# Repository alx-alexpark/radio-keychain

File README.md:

# radio-keychain
A fully-functional FM receiver in a 3x3cm footprint, perfect for a keychain.

It uses the connected headphones as an antenna, and is powered off a CR2032 coin cell. The FM tuner used is the Si4702, which supports the 76-108MHz frequency range.

Based on the CH32v003, this radio runs on RISC-V!

## Motivation
I love radio, and I wanted to make the tiniest keychain radio possible. I also thought it would be interesting to learn how radios work.

## How to use
First, connect a pair of headphones or an aux cable, this is your antenna. There are 4 buttons on the device, a volume up/down, and a frequency up/down. First, set the volume to a confortable level, and then use the frequency up/down buttons to step up and down 0.1MHz until you find a station. Then, enjoy listening to the station!

## Schematic and PCB
https://kicanvas.org/?repo=https://github.com/alx-alexpark/radio-keychain

## Zine

## Bill of Materials

| Designator | Footprint | Quantity | Value | LCSC Part # |
|---|---|---|---|---|
| BT1 | BAT-SMD_MY-2032-12 | 1 | MY-2032-12 | [C964833](https://www.lcsc.com/product-detail/C964833.html) |
| C1, C6 | 0402 | 2 | 100nF | [C1525](https://www.lcsc.com/product-detail/C1525.html) |
| C2 | 0402 | 1 | 100pF | [C1546](https://www.lcsc.com/product-detail/C1546.html) |
| C3, C4 | 0603 | 2 | 0.47uF | [C1623](https://www.lcsc.com/product-detail/C1623.html) |
| C5, C7, C8 | 0603 | 3 | 1uF | [C1592](https://www.lcsc.com/product-detail/C1592.html) |
| C9 | 0402 | 1 | 22nF | [C1532](https://www.lcsc.com/product-detail/C1532.html) |
| CN1 | PJ-320D | 1 | PJ-320D | [C431535](https://www.lcsc.com/product-detail/C431535.html) |
| D1 | 0402 | 1 | LED | [C2286](https://www.lcsc.com/product-detail/C2286.html) |
| FB1, FB2 | 0603 | 2 | BLM18BD252SN1D | [C77668](https://www.lcsc.com/product-detail/C77668.html) |
| J1 | PinHeader_1x03_P2.54mm_Vertical | 1 | Conn_01x03_Pin | — |
| L1 | 0603 | 1 | LQW18ANR27J00D | [C98093](https://www.lcsc.com/product-detail/C98093.html) |
| OSC1 | CRYSTAL-SMD_4P-L3.2-W2.5-BL | 1 | SX2M32_768KM20F30TNN | [C2901603](https://www.lcsc.com/product-detail/C2901603.html) |
| R1, R2, R3, R4, R5, R6 | 0603 | 6 | 10k | [C25804](https://www.lcsc.com/product-detail/C25804.html) |
| R10, R9 | 0402 | 2 | 2k | [C4109](https://www.lcsc.com/product-detail/C4109.html) |
| R11 | 0402 | 1 | 330 | [C25104](https://www.lcsc.com/product-detail/C25104.html) |
| R7, R8 | 0402 | 2 | 2.2k | [C25879](https://www.lcsc.com/product-detail/C25879.html) |
| SW1, SW2, SW3, SW4 | SW-SMD_4P-L4.2-W3.3-P2.15-LS5.1 | 4 | SW_Push_45deg | [C455282](https://www.lcsc.com/product-detail/C455282.html) |
| SW5 | SW-SMD_MST22D18G2 | 1 | K3-2235S-F1 | [C223858](https://www.lcsc.com/product-detail/C223858.html) |
| U1 | QFN-20-1EP_3x3mm_P0.4mm_EP1.65x1.65mm | 1 | CH32V003F4U6 | [C5299908](https://www.lcsc.com/product-detail/C5299908.html) |
| U2 | QFN-28_4x4mm_P0.5mm | 1 | TPA6130A2RTJR | [C130046](https://www.lcsc.com/product-detail/C130046.html) |
| U3 | MPS_QFN-16_3x3mm_P0.5mm | 1 | SI4702-C19-GMR | [C2155666](https://www.lcsc.com/product-detail/C2155666.html) |

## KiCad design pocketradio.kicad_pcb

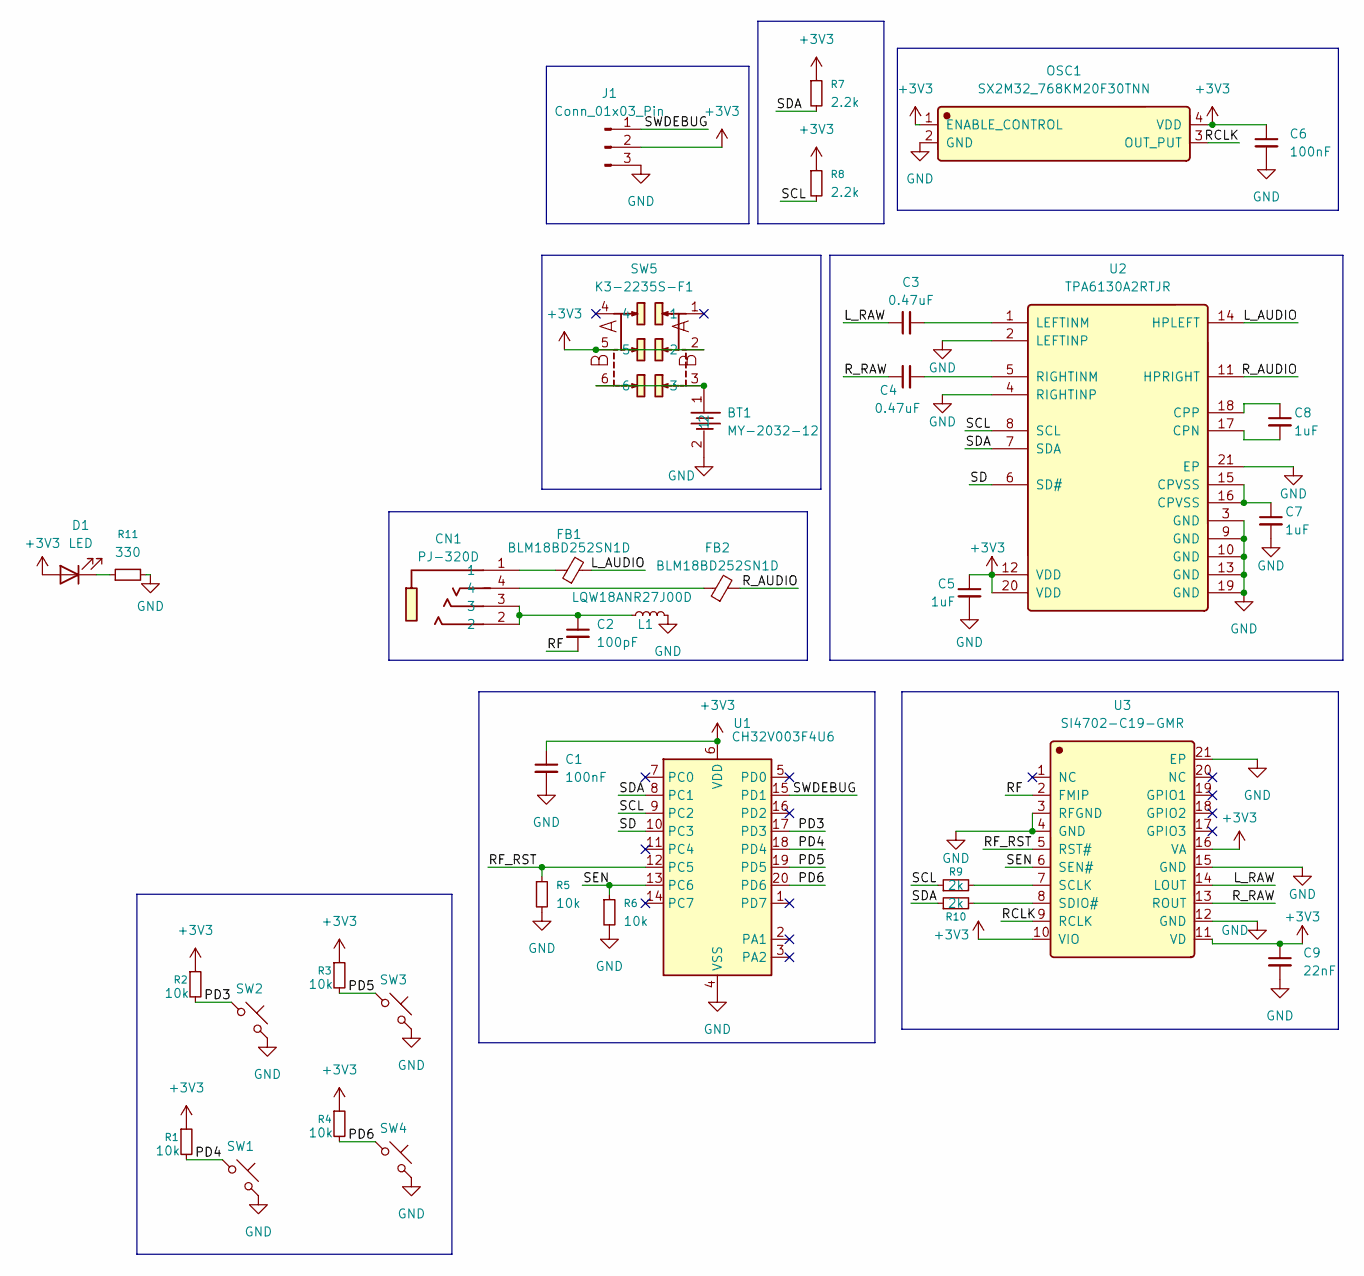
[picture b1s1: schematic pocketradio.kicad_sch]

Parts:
BT1: MY-2032-12; BAT-SMD_MY-2032-12; Manufacturer Part MY-2032-12; LCSC C964833
C1, C6: 100nF; C_0402_1005Metric; LCSC Part C1525
C2: 100pF; C_0402_1005Metric; LCSC Part C1546
C3, C4: 0.47uF; C_0603_1608Metric; LCSC Part C1623
C5, C7, C8: 1uF; C_0603_1608Metric; LCSC Part C1592
C9: 22nF; C_0402_1005Metric; LCSC Part C1532
CN1: PJ-320D; Manufacturer Part PJ-320D; LCSC C431535
D1: LED; LED_0402_1005Metric; LCSC Part C2286
FB1, FB2: BLM18BD252SN1D; L_0603_1608Metric; LCSC Part C77668
J1: Conn_01x03_Pin; PinHeader_1x03_P2.54mm_Vertical
L1: LQW18ANR27J00D; L_0603_1608Metric; LCSC Part C98093
OSC1: SX2M32_768KM20F30TNN; CRYSTAL-SMD_4P-L3.2-W2.5-BL; Manufacturer Part SX2M32.768KM20F30TNN; LCSC C2901603
R1, R2, R3, R4, R5, R6: 10k; R_0603_1608Metric; LCSC Part C25804
R7, R8: 2.2k; C_0402_1005Metric; LCSC Part C25879
R9, R10: 2k; R_0402_1005Metric; LCSC Part C4109
R11: 330; R_0402_1005Metric; LCSC Part C25104
SW1, SW2, SW3, SW4: SW_Push_45deg; SW-SMD_4P-L4.2-W3.3-P2.15-LS5.1; LCSC Part C455282
SW5: K3-2235S-F1; SW-SMD_MST22D18G2; Manufacturer Part K3-2235S-F1; LCSC C223858
U1: CH32V003F4U6; QFN-20-1EP_3x3mm_P0.4mm_EP1.65x1.65mm; LCSC C5299908
U2: TPA6130A2RTJR; QFN-28_4x4mm_P0.5mm; Manufacturer Part TPA6130A2RTJR; LCSC C130046
U3: SI4702-C19-GMR; MPS_QFN-16_3x3mm_P0.5mm; Manufacturer Part SI4702-C19-GMR; LCSC C2155666

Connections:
+3V3: C1.1, C5.1, C6.1, C9.1, D1.2 (A), J1.2, OSC1.1 (ENABLE_CONTROL), OSC1.4 (VDD), R1.1, R2.1, R3.1, R4.1, R7.1, R8.1, SW5.2, SW5.5, U1.6 (VDD), U2.12 (VDD), U2.20 (VDD), U3.10 (VIO), U3.11 (VD), U3.16 (VA)
/L_AUDIO: FB1.2, U2.14 (HPLEFT)
/L_RAW: C3.1, U3.14 (LOUT)
/PD3: R2.2, SW2.1, U1.17 (PD3)
/PD4: R1.2, SW1.1, U1.18 (PD4)
/PD5: R3.2, SW3.1, U1.19 (PD5)
/PD6: R4.2, SW4.1, U1.20 (PD6)
/RCLK: OSC1.3 (OUT_PUT), U3.9 (RCLK)
/RF: C2.2, U3.2 (FMIP)
/RF_RST: R5.1, U1.12 (PC5), U3.5 (RST#)
/R_AUDIO: FB2.2, U2.11 (HPRIGHT)
/R_RAW: C4.1, U3.13 (ROUT)
/SCL: R8.2, R9.1, U1.9 (PC2), U2.8 (SCL)
/SD: U1.10 (PC3), U2.6 (SD#)
/SDA: R7.2, R10.1, U1.8 (PC1), U2.7 (SDA)
/SEN: R6.1, U1.13 (PC6), U3.6 (SEN#)
/SWDEBUG: J1.1, U1.15 (PD1)
GND: BT1.2, C1.2, C5.2, C6.2, C7.2, C9.2, J1.3, L1.2, OSC1.2 (GND), R5.2, R6.2, R11.2, SW1.2, SW2.2, SW3.2, SW4.2, U1.4 (VSS), U1.21 (VSS), U2.2 (LEFTINP), U2.3 (GND), U2.4 (RIGHTINP), U2.9 (GND), U2.10 (GND), U2.13 (GND), U2.19 (GND), U2.21 (EP), U3.3 (RFGND), U3.4 (GND), U3.12 (GND), U3.15 (GND), U3.21 (EP)
unnamed: BT1.1, SW5.3, SW5.6
unnamed: C2.1, CN1.2, CN1.3, L1.1
unnamed: C7.1, U2.15 (CPVSS), U2.16 (CPVSS)
unnamed: CN1.1, FB1.1
unnamed: CN1.4, FB2.1
unnamed: D1.1 (K), R11.1
unnamed: C8.2, U2.17 (CPN)
unnamed: C8.1, U2.18 (CPP)
unnamed: C3.2, U2.1 (LEFTINM)
unnamed: C4.2, U2.5 (RIGHTINM)
unnamed: R9.2, U3.7 (SCLK)
unnamed: R10.2, U3.8 (SDIO#)

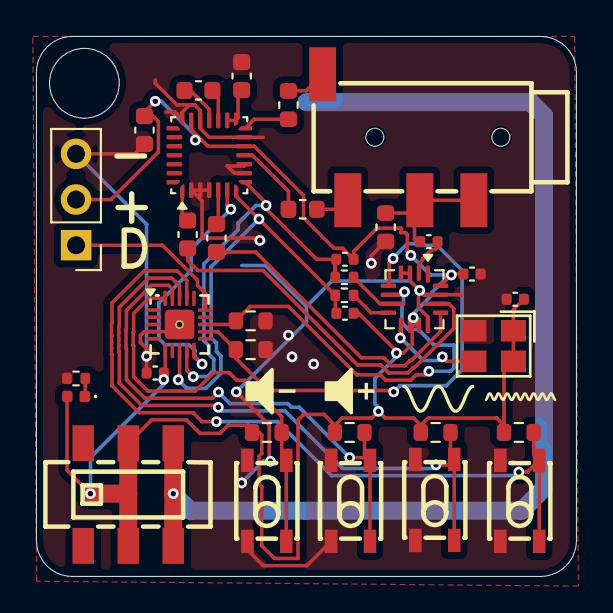
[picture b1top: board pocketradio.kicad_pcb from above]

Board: 2 copper layers, 30.0 x 30.0 mm, 36 parts (1 on the bottom side), 30 nets.

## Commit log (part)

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2026-04-05 lots of stuff
2026-04-07 power LED
2026-04-07 recheck audio jack pinou
2026-04-07 basic readme
2026-04-07 remove .history
2026-04-26 change a few things
2026-04-26 add prod files
2026-04-26 sussy
2026-04-26 reorganize files
2026-04-26 move folder
